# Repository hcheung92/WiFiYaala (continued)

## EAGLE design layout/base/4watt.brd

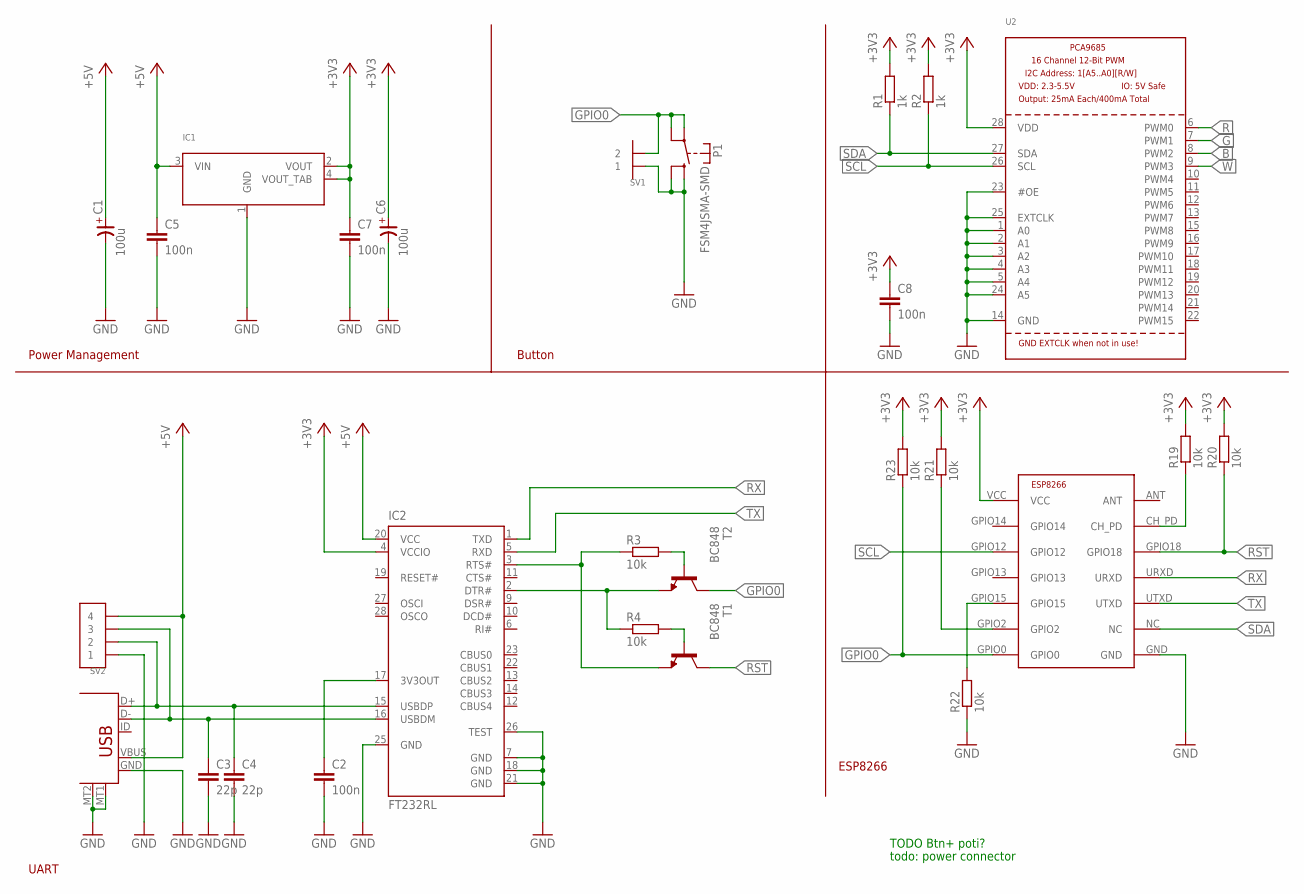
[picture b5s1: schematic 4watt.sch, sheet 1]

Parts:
C1, C6: 100u; 7343-TE-D
C2, C5, C7, C8: 100n; C0603
C3, C4: 22p; C0603
IC1: LM1117IMP; SOT223
IC2: FT232RL; SSOP28
P1: FSM4JSMA-SMD
R1, R2: 1k; R0603
R3, R4, R19, R20, R21, R22, R23: 10k; R0603
SV1: 1X2SMD-2.54LIEGEND
SV2: 1X4SMD-2.54LIEGEND
T1, T2: BC848; SOT23
U2: PCA9685; TSSOP28
U$2: ESP8266; ESP-03
U$40: USB-B; USB-MICROB

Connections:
+3V3: C6.+, C7.1, C8.1, IC1.2 (VOUT), IC1.4 (VOUT_TAB), IC2.4 (VCCIO), R1.2, R2.2, R19.2, R20.2, R21.2, R23.2, U2.28 (VDD), U$2.VCC
+5V: C1.+, C5.1, IC1.3 (VIN), IC2.20 (VCC), SV2.P$4 (4), U$40.VBUS; also elsewhere on the board
B: U2.8 (PWM2); also elsewhere on the board
G: U2.7 (PWM1); also elsewhere on the board
GND: C1.-, C2.2, C3.2, C4.2, C5.2, C6.-, C7.2, C8.2, IC1.1 (GND), IC2.7 (GND), IC2.18 (GND), IC2.21 (GND), IC2.25 (GND), IC2.26 (TEST), P1.P$3 (S), P1.P$4 (S), R22.1, SV1.P$1 (1), SV2.P$1 (1), U2.1 (A0), U2.2 (A1), U2.3 (A2), U2.4 (A3), U2.5 (A4), U2.14 (GND), U2.23 (#OE), U2.24 (A5), U2.25 (EXTCLK), U$2.GND, U$40.GND, U$40.MT1, U$40.MT2; also elsewhere on the board
GPIO0: P1.P$1, P1.P$2, R23.1, SV1.P$2 (2), T2.3 (C), U$2.GPIO0
GPIO15: R22.2, U$2.GPIO15
unnamed: IC2.3 (RTS#), R3.1, T1.2 (E)
unnamed: R19.1, U$2.CH_PD
unnamed: C4.1, IC2.15 (USBDP), SV2.P$2 (2), U$40.D+
unnamed: C3.1, IC2.16 (USBDM), SV2.P$3 (3), U$40.D-
unnamed: IC2.2 (DTR#), R4.1, T2.2 (E)
unnamed: R21.1, U$2.GPIO2
unnamed: R3.2, T2.1 (B)
unnamed: R4.2, T1.1 (B)
unnamed: C2.1, IC2.17 (3V3OUT)
R: U2.6 (PWM0); also elsewhere on the board
RST: R20.1, T1.3 (C), U$2.GPIO18
RX: IC2.1 (TXD), U$2.URXD
SCL: R2.1, U2.26 (SCL), U$2.GPIO12
SDA: R1.1, U2.27 (SDA), U$2.NC
TX: IC2.5 (RXD), U$2.UTXD
W: U2.9 (PWM3); also elsewhere on the board

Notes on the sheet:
Power Management
Button
UART
ESP8266
TODO Btn+ poti?
todo: power connector

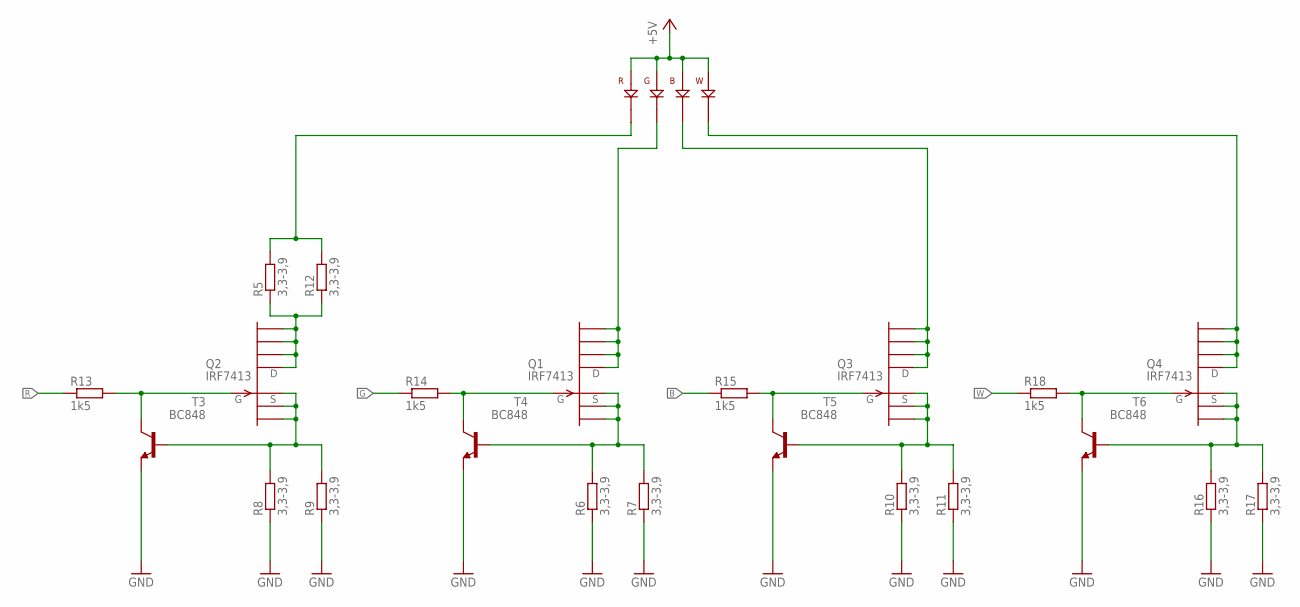
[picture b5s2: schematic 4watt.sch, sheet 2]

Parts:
LED1: JH-4RGBW14G30-E2A
Q1, Q2, Q3, Q4: IRF7413; SO-8
R5, R6, R7, R8, R9, R10, R11, R12, R16, R17: 3,3-3,9; M1206
R13, R14, R15, R18: 1k5; R0603
T3, T4, T5, T6: BC848; SOT23

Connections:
+5V: LED1.B+, LED1.G+, LED1.R+, LED1.W+; also elsewhere on the board
B: R15.1; also elsewhere on the board
G: R14.1; also elsewhere on the board
GND: R6.1, R7.1, R8.1, R9.1, R10.1, R11.1, R16.1, R17.1, T3.2 (E), T4.2 (E), T5.2 (E), T6.2 (E); also elsewhere on the board
unnamed: Q2.1 (S), Q2.2 (S1), Q2.3 (S2), R8.2, R9.2, T3.1 (B)
unnamed: Q2.5 (D), Q2.6 (D1), Q2.7 (D2), Q2.8 (D3), R5.1, R12.1
unnamed: Q4.4 (G), R18.2, T6.3 (C)
unnamed: Q4.1 (S), Q4.2 (S1), Q4.3 (S2), R16.2, R17.2, T6.1 (B)
unnamed: LED1.W-, Q4.5 (D), Q4.6 (D1), Q4.7 (D2), Q4.8 (D3)
unnamed: Q2.4 (G), R13.2, T3.3 (C)
unnamed: LED1.R-, R5.2, R12.2
unnamed: Q1.4 (G), R14.2, T4.3 (C)
unnamed: Q1.1 (S), Q1.2 (S1), Q1.3 (S2), R6.2, R7.2, T4.1 (B)
unnamed: LED1.G-, Q1.5 (D), Q1.6 (D1), Q1.7 (D2), Q1.8 (D3)
unnamed: Q3.4 (G), R15.2, T5.3 (C)
unnamed: Q3.1 (S), Q3.2 (S1), Q3.3 (S2), R10.2, R11.2, T5.1 (B)
unnamed: LED1.B-, Q3.5 (D), Q3.6 (D1), Q3.7 (D2), Q3.8 (D3)
R: R13.1; also elsewhere on the board
W: R18.1; also elsewhere on the board

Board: 2 copper layers, 50 parts (0 on the bottom side), 36 nets, no tracks yet.

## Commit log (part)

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2014-12-22 Hello world, this is WiFiYaala
2014-12-22 cleanup
2014-12-22 improved visability
2014-12-22 improved
2014-12-28 base schematic
2014-12-29 added raw lua firmware
2014-12-29 reset to clean state
2014-12-29 removed
2014-12-29 Squashed 'firmware-lua/' content from commit 3e25a10
    git-subtree-dir: firmware-lua
    git-subtree-split: 3e25a1059ba41ba075ef396431f2fe1bdfec0068
2014-12-29 binary separation and uploading added
2014-12-29 added missing includes
2014-12-29 dhcp dns name hack
2014-12-29 led started
2014-12-29 init
2014-12-29 hostname set and gt
2014-12-30 lua led module working
2014-12-30 led stuff
2014-12-30 Squashed 'firmware-lua/' changes from 3e25a10..72f60d3
    72f60d3 rebuild bin, add setip, setmac, sleeptype api to wifi module, fix #62
    a2e357f Merge pull request #64 from alonewolfx2/patch-1
    c7e83e5 build bins
    26a554f for set wifi issue
    4cf5265 deal with uart.on api when required char number is 0
    265d270 Merge pull request #63 from nodemcu/dev094
2014-12-30 base schematic w/o IC3 but w/ all dev board holes
2014-12-30 gitignore added
2015-01-04 Added ESP8266 library
2015-01-04 LuaLoader init
2015-01-04 APA102 testcase
2015-01-04 revision required
2015-01-04 mising files
2015-01-05 4watt led init -- not routed
2015-01-05 esp-03 added
2015-01-05 new pinout
2015-01-05 extclk to gnd
2015-01-05 directory changed
2015-01-06 Added unfinished layout for single color stripe PCB. Added library for specific connectors and transistors.
2015-01-06 not quite there
2015-01-06 ws28xx output and 2 additional RGBW led connectors
2015-01-06 not quite their
2015-01-06 LDO regulator added
2015-01-07 ws28xx signal converter
2015-01-07 git ignore added
2015-01-07 right before v0.9.5
2015-01-07 before ws281x converter
2015-01-09 power rails done
2015-01-10 challenge accepted and passed
2015-01-11 Finished layout for 4*RGBW stripe v1.0
2015-01-11 Added con-yaala eagle library
2015-01-11 DRC errors and airwires in onecolor stripe removed.
2015-01-11 Added naming for onecolor stripe layout
2015-01-11 changed numbering
2015-01-11 added doku layer
2015-01-11 removed drcs
2015-01-11 files moved. replace by tag
2015-01-11 Squashed 'firmware-lua/' changes from 72f60d3..2709258
    2709258 using esptool.py in all platform, fix makefile on windows
    bc33967 Merge pull request #89 from sej7278/master
    56daed7 Merge pull request #88 from baracudaz/master
    a1e9e58 Vastly simplified generating and flashing firmware.
    6525747 DS18B20 module examples
    a0f5559 Merge pull request #81 from nodemcu/dev095
2015-01-11 nodemcu merge
2015-01-11 minor adjustments to the makefile
2015-01-16 basic file upload work. a lot of robustness features including error handling still missing
2015-01-17 Fileupload working
2015-01-17 File browser gui
2015-01-17 LuaLoader DEPRICATED before arrival. Development stop in favour of ESPlorer.
2015-01-18 prepaired new structure
2015-01-18 adjusted script in order to be compatible with the nodemcu-dev schematic
2015-01-18 Squashed 'firmware-lua/' changes from 2709258..df3c823
    df3c823 add spi, and some minor fix
    262f831 Merge pull request #107 from iabdalkader/spi
    3c16014 Add SPI Module
    35d2b9e Fixed description of Connect to your ap.
    a2d1e5f move eclipse project file to root, now eclipse can see all files
    59a67e5 Merge pull request #94 from kmpm/esptool
2015-01-20 revised LED interface. pca9685 done. apa102 in progress. ws28xx pending
2015-01-20 optimized/minimized i2c communication; removed pwm glitches
2015-01-21 Select PIN functionality added
2015-01-22 Bauteilbeschriftung der Platinen base und 4watt geordnet. Bestückungspläne hinzugefügt.
2015-01-22 Schaltpläne hinzugefügt
2015-01-23 added final bins
2015-01-25 ws28xx converter bugfix + testsoftware
2015-01-26 corrected formating
2015-01-26 Squashed 'firmware-lua/' changes from df3c823..b6185c8
    b6185c8 add udp example to readme
    afa741c Update changelog 2015-01-27.
    6b7d113 Delete mistake changelog.
    2c4e40d Update changelog 2015-01-26.
    5ca3765 Merge pull request #136 from nodemcu/devfloat
    c39deb2 Turn floating point option ON. Add pre_build/0.9.5/nodemcu_20150127.bin.
2015-01-28 new 4watt ikea kvarna case
2015-01-28 single led init bugfix
2015-01-30 typo
2015-01-30 Squashed 'firmware-lua/' changes from b6185c8..5894df1
    5894df1 Combined dsleep_set_options(option) to dsleep( us, option ) * dsleep( us, option ) Hardware has to support deep-sleep wake up (XPD_DCDC connects to EXT_RSTB with 0R). system_deep_sleep(0) ，se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
2015-01-30 ws28xx framework init. current problem: tx fifo
2015-02-01 ws281x working (hardware fifo), some glitches fir the ws2801 still remain
2015-02-01 removed debug output
2015-02-01 ws2801 bugfix
2015-02-02 added some lua scripts fade.lua: fades some random colors candle.lua: emulates a candle lib.lua: common functions -> should be written in c init.lua: my initialization -> should be improved
2015-02-03 Delete init.lua
    everybody should have his own init.lua
2015-02-03 Create Readme.md
    the template for a init file, will be improved by server and so on
2015-02-03 init.lua ignore
2015-02-03 demo.lua: some crazy color fadings showing time and HSL-capabilities
2015-02-03 added ignore for ESPlorer/
2015-02-04 9600 test
2015-02-04 fixed structure of lua files, new programming style candle.lua: candle demo demo.lua: demo flashy crap fade.lua: fading random colors lib.lua: library functions init.lua: init wifi, button, programs 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
2015-02-11 Squashed 'firmware-lua/' changes from 5894df1..370bc88
    370bc88 Merge pull request #198 from Ivoah/patch-1
    b33e44c Update telnet.lua
    90f3401 Merge pull request #197 from nodemcu/revert-182-patch-2
    7f633b9 Revert "Use python2 instead of python(2/3)"
    dec47d5 fix #185
    7f970df Merge pull request #182 from lukas2511/patch-2
2015-02-11 its compiling gain
2015-02-13 basic webserver working (download only)
2015-02-13 file browser works (view only)
2015-02-13 file browser delete is working
2015-02-13 file browser somewhere in upload
2015-02-14 file browser complete (debug output)
2015-02-14 fixed caching issues
2015-02-14 lua post hook
2015-02-14 new line bug removed
2015-02-15 html form bug
2015-02-15 lua back and forth
2015-02-15 example for transmitting lua command to the esp
2015-02-15 Schaltplan für ledChain hinzugefügt. Bauteilbezeichnungen sortiert.
2015-02-16 added more notes
2015-02-16 lua2hhtp working. debug output removed
2015-02-16 http+lua working
2015-02-16 clean build
2015-02-16 Squashed 'firmware-lua/' changes from 370bc88..7e524f7
    7e524f7 Merge pull request #213 from nodemcu/cross
    2e2742c Merge pull request #212 from ksankark/patch-1
    6e840a4 add node.compile() api
    a58f50e Update irsend.lua
    3b80bc4 Merge pull request #209 from nodemcu/dev
    059a5ee wifi.ap.setip() can set ip address now, fixed #199.
2015-02-16 Added batch to flash bin from Windows
2015-02-17 trying to shrink programs added python2.7 to Makefile
2015-02-17 fixed program-style + added lc Programs now are module that are loded and unloaded on change (handled by programs.lc) the active program is stored under programs.active and must be run with programs.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
2015-02-17 added python2.7 for Makefile
2015-02-17 missed program p_candle.lc
2015-02-17 added a simple index.html with ajax
2015-02-17 reduced led freq to 50hz
2015-02-17 adjusted file to meet http specs
2015-02-17 reduced led priority to 0
2015-02-17 prio 0 not working
2015-02-17 prio0
2015-02-17 led software test
2015-02-18 tried to fix sending lua command via xmlhttprequest -> need change in httpd.c
2015-02-18 Squashed 'firmware-lua/' changes from 7e524f7..94aa3be
    94aa3be Merge pull request #227 from robcazzaro/patch-1
    8572748 Update dht22.lua
    git-subtree-dir: firmware-lua
    git-subtree-split: 94aa3bef17e76e2dae96d34795f82749b230b4c8
2015-02-18 improved boundary detection, introduced gzip file support
2015-02-18 improved index.html now using jQuery.jsz
2015-02-18 improved color set in index.html
2015-02-18 no delay for init
2015-02-20 Improved high level led functionality: - Lua module is now with range for all functions. - Error messages more differentiated - New functions led.get() and led.inited()
2015-02-20 fixed programs for new led.*(range) improved index.html
2015-02-21 now using minified.js instead of jQuery.js (similar but much smaller) - right now no colorchooser -> will use simple drag - moved js and css from index to own files (need to be minimized and gziped) 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
2015-02-21 background now is used as colorpicker - x < 100px: lightness - else: x=hue, y=saturation some more improvements to come
2015-02-21 Improved range check for led functions. Negative indices to address from last. Added first programs for multicolor stripes.
2015-02-21 added landscape support improved colorchoosing on mobile browsers
2015-02-21 adapted programs to new modulo-range-based set led
2015-02-21 added windows flash script
2015-02-21 removed old js libraries
2015-02-22 fixed off command and click-propagation
2015-02-22 set hostname to "WiFiYaala"
2015-02-23 Again improved lua led commands. Now stripe behaves as one endles loop. Writing behind last led will start from begining. Updated p_chaser for new led functionality. removed fail function with startu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
2015-02-26 New multicolor stripe program with rainbow fading.
2015-03-01 Squashed 'firmware-lua/' changes from 94aa3be..84a9ab3
    84a9ab3 Merge pull request #251 from makefu/patch-1
    194ee39 Fix Pinout HTML table layout
    e60e4f1 Merge pull request #236 from dMbski/patch-1
    888fbdf ver 0.9.5 reports error in tmr.alarm()
    git-subtree-dir: firmware-lua
    git-subtree-split: 84a9ab35a8eb9b4ae2229bba7b2626c2a285818d
2015-03-01 bins recomiled after merge
2015-03-08 use config.lc to init your hardware
2015-03-09 Added defines to switch between hardware and software timer for led handling.
2015-03-09 Added math to lua. Not all functions are working, but some very usefull for led programs. For example math.random() math.min() math.max(). Trigonometric functions are not working because math.h not w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
    Added new multicolor program p_rangefade.lua
2015-03-09 added basic support for properties via web-interface
2015-03-09 added p_candle.lc after settings changes
2015-03-12 Added a multicolor program, simulating a sunrise.
2015-03-12 fixed program inactivation tried to improve stability
2015-03-14 fixed memory-problem with loading several programs introduced brightess on button
2015-03-14 Squashed 'firmware-lua/' changes from 84a9ab3..a816622
    a816622 update readme
    8638863 update readme
    9f006ac update readme
    4cb8d95 Merge pull request #275 from gitter-badger/gitter-badge
    4005723 Added Gitter badge
    6986d9e update travis.yml
2015-03-14 freed program ram space by 50bytes
2015-03-15 moved non-lua-files from lua/ to gui/ also introducing releases/ folder containing links to files to be used for different WiFiYaala plattforms.
2015-03-16 Little more heap by deactivating unneeded Lua modules: OW, BIT, SPI, ADC
2015-03-16 hl2rgb now in led.hsl2rgb. lib.lua no longer necessary
2015-03-27 Squashed 'firmware-lua/' changes from a816622..1bd3f56
    1bd3f56 Merge pull request #297 from nodemcu/dev
    3d14530 fix cjson.encode() when in integer version
    3aead6d try to fix cjson.encode in integer only version
    a61cbfb Merge pull request #295 from nodemcu/master
    a707092 merge cjson and dev to master, make a stable release
    a01bda0 Merge pull request #294 from nodemcu/json
2015-03-27 revised merge bugs
2015-03-28 ram segment is fitting again
2015-03-29 changed file modes
2015-03-29 fixed bugs with parameters: not loading, not removing after program change
2015-03-29 improved network stability added overlay on network problems
2015-03-30 adjusted timing in order to prevent simultanious execution of p.dofile and p.dounload
2015-04-06 mqtt enabled
2015-04-11 Squashed 'firmware-lua/' changes from 1bd3f56..e61ad9d
    e61ad9d Merge pull request #339 from wladurner/issue_321
    4ac5aba Merge pull request #338 from MarsTechHAN/patch-1
    9df94c7 Really Fix the BUGs, add come comment
    560ad8e remove dht22 lib, use dht_lib instead
    fee2cf4 Merge branch 'master' into dev
    450b79d add more mqtt example, add a mqtt subfolder
2015-04-11 started to implement prog.*
